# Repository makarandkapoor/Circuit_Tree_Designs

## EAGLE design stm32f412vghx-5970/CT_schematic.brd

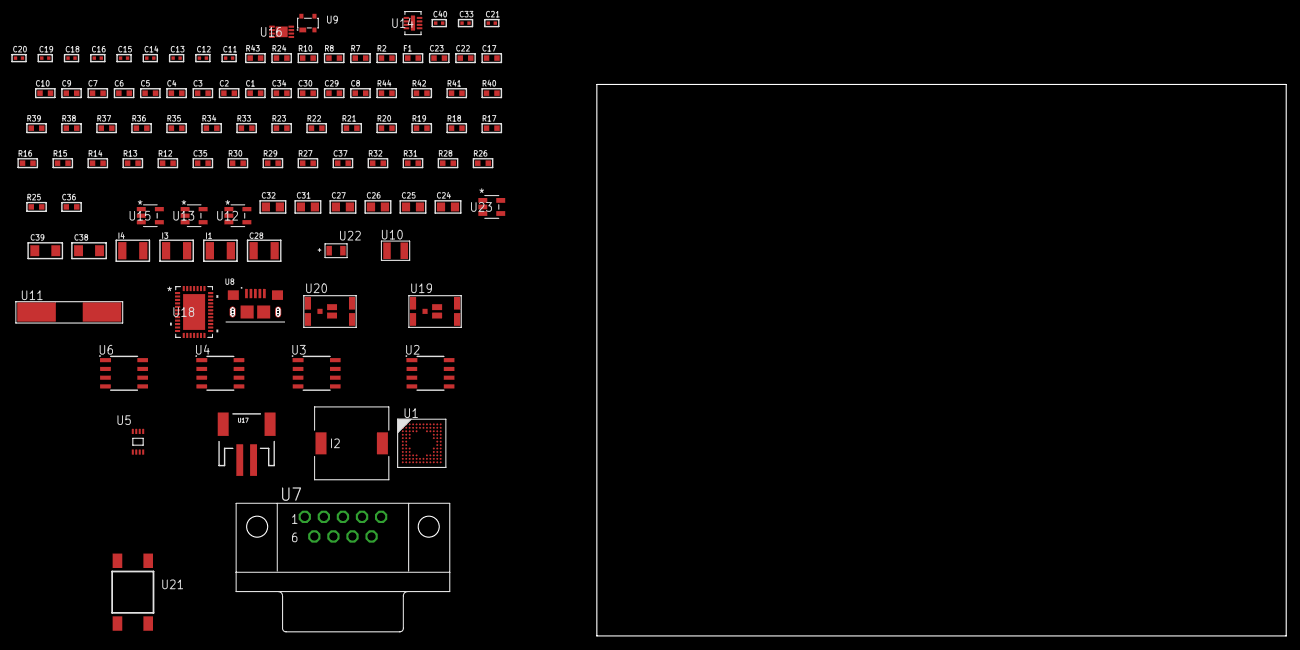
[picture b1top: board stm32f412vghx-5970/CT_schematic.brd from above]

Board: 2 copper layers, 105 parts (0 on the bottom side), 76 nets, no tracks yet.

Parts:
C1, C10, C17, C22, C23: 1e-06; C0603
C2, C3, C4, C5, C6, C7: 1e-07; C0603
C8: 4.7e-06; C0603
C9: 1e-08; C0603
C11, C12, C33: 1e-07; C0402
C13, C14, C15, C16: 1e-11; C0402
C18, C19, C20, C21, C40: 1e-08; C0402
C24, C25, C26, C27, C31, C32: 1e-05; C0805
C28: 1e-05; C1210
C29, C34: 2.2e-06; C0603
C30: 2.2e-07; C0603
C35: 2.45e-08; R0603
C36: 2.8258362168397e-09; R0603
C37: 7.105e-09; R0603
C38, C39: 1e-05; C1206
F1: 240.0; L0603
I1, I4: 3.3e-05; L1210
I2: 7e-06; DR1040
I3: 1e-05; L1210
R2: 1000.0; R0603
R7: 4700.0; R0603
R8, R10: 2200.0; R0603
R12, R13, R14, R15, R16, R17, R18, R19, R20, R21, R22, R23, R33, R35, R36, R39, R40, R41, R44: 10000.0; R0603
R24: 120.0; R0603
R25, R26, R28, R31, R32: 1000000.0; R0603
R27: 490000.0; R0603
R29: 100000.0; R0603
R30: 560000.0; R0603
R34: 75000.0; R0603
R37, R38: 95300.0; R0603
R42: 24000.0; R0603
R43: 2000.0; R0603
U1: STM32F412VGH6; UFBGA100
U2: AT25080B-SSHL-T; SOIC-8
U3: AT25320B-SSHL-T; SOIC-8
U4: AT25512N-SH-T; SOIC-8
U5: 24AA08T-I/MNY; TDFN-8/6MM
U6: MCP2562-E/SN; SOIC-8
U7: 182-009-113R531; 182-009-MALE
U8: 10118193-0001LF; FCI_10118193-0001LF
U9: prtr5v0u2ax; SOT143B
U10: ABS07-32.768KHZ-7-T
U11: ABLS-25.000MHZ-B2F-T
U12, U13, U15: ltc3406es5; TSOT-23-5
U14: LT3494AEDDB#TRMPBF; DFN-8_DDB
U16: MCP73831T-2ACI/MC; DFN8_2X3MC
U17: S2B-PH-SM4-TB(LF)(SN); JST-2-SMD
U18: LTC2928CUHF#PBF; QFN-38_UHF
U19, U20: IRF8306MTRPbF; IRF8306MTRPBF
U21: 4-1437565-2; SW_4-1437565-2
U22: Q65110A2395; LGM67K-G1J2-24-Z
U23: nc7sz125m5x; NC7SZ125M5X

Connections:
CLK_CRYSTAL_U1_D1: C13.1, U1.D1, U10.1
CLK_CRYSTAL_U1_E1: C14.1, U1.E1, U10.2
CLK_CRYSTAL_U1_F1: C15.1, U1.F1, U11.1
CLK_CRYSTAL_U1_G1: C16.1, U1.G1, U11.2
GND: C1.2, C2.2, C3.2, C4.2, C5.2, C6.2, C7.2, C8.2, C9.2, C10.2, C11.2, C12.2, C13.2, C14.2, C15.2, C16.2, C17.2, C18.2, C19.2, C20.2, C21.2, C22.2, C23.2, C24.2, C25.1, C25.2, C26.2, C27.1, C27.2, C28.2, C29.2, C30.2, C31.2, C32.1, C32.2, C33.2, C34.2, C35.2, C36.2, C37.2, C38.2, C39.2, C40.2, R2.2, R12.2, R13.2, R25.2, R27.2, R31.2, R34.2, R37.2, R38.2, R39.2, R40.2, R41.2, R43.2, U1.B12, U1.D3, U1.F2, U1.F11, U1.F12, U1.J1, U1.K1, U2.4, U3.4, U4.4, U5.4, U6.2, U6.8, U7.5, U8.5, U8.6, U8.7, U8.8, U8.9, U9.1, U12.2, U13.2, U14.2, U14.9, U15.2, U16.6, U16.9, U17.2, U18.8, U18.9, U18.10, U18.12, U18.13, U18.24, U18.25, U18.30, U18.32, U18.39, U22.C, U23.1, U23.3
INPUT_USBPOWER_5V: C17.1, C38.1, R44.2, U1.D10, U8.1, U9.4, U16.1, U16.2
NET_U1_A3: R8.1, U1.A3, U5.6
NET_U1_A4: R12.1, U1.A4
NET_U1_B3: R10.1, U1.B3, U5.5
NET_U1_C11: C12.1, U1.C11
NET_U1_E3: R14.1, U1.E3
NET_U1_H2: R7.1, U1.H2, U23.4
NET_U1_H3: R13.1, U1.H3
NET_U1_M1: C9.1, C10.1, F1.1, U1.L1, U1.M1
NET_U1_M12: U21.3, U21.4
NET_U2_3: R15.1, U2.3
NET_U2_7: R17.1, U2.7
NET_U3_3: R18.1, U3.3
NET_U3_7: R20.1, U3.7
NET_U4_3: R21.1, U4.3
NET_U4_7: R23.1, U4.7
NET_U6_6: R24.2, U6.6
NET_U7_2: R24.2, U6.6, U7.2
NET_U7_3: R24.1, U6.7, U7.3
NET_U12_3: I1.1, U12.3
NET_U12_5: R25.1, R26.1, U12.5
NET_U12_ATNET_3: I1.2, R26.2
NET_U13_3: I2.1, U13.3
NET_U13_5: R27.1, R28.1, U13.5
NET_U13_ATNET_3: I2.2, R28.2
NET_U14_1: I3.1, U14.1
NET_U14_5: R29.1, U14.5
NET_U14_6: R30.1, U14.6
NET_U14_8: C30.1, U14.8
NET_U15_3: I4.1, U15.3
NET_U15_5: R31.1, R32.1, U15.5
NET_U15_ATNET_3: I4.2, R32.2
NET_U16_5: R44.1, U16.5
NET_U16_8: R43.1, U16.8
NET_U18_3: R40.1, U18.3
NET_U18_6: R37.1, U18.6
NET_U18_7: R38.1, U18.7
NET_U18_16: R39.1, R42.1, U18.16
NET_U18_18: R36.1, U18.18
NET_U18_19: R35.1, U18.19, U18.20
NET_U18_21: R33.1, R34.1, U18.21, U23.2
NET_U18_26: C36.1, U18.26
NET_U18_27: C35.1, U18.27
NET_U18_28: C37.1, U18.28
NET_U18_38: R41.1, U18.38
NET_U19_3: U18.2, U19.3
NET_U20_3: U18.37, U20.3
NET_U21_1: R2.1, U21.1, U21.2
PROC_CAN1_RX: U1.C9, U6.4
PROC_CAN1_TX: U1.B9, U6.1
PROC_SPI1_MISO: U1.A7, U2.2
PROC_SPI1_MOSI: U1.C5, U2.5
PROC_SPI1_NSS: R16.1, U1.A9, U2.1
PROC_SPI1_SCK: U1.A8, U2.6
PROC_SPI2_MISO: U1.J3, U4.2
PROC_SPI2_MOSI: U1.K2, U4.5
PROC_SPI2_NSS: R22.1, U1.L12, U4.1
PROC_SPI2_SCK: U1.B8, U4.6
PROC_SPI3_MISO: U1.C10, U3.2
PROC_SPI3_MOSI: U1.B6, U3.5
PROC_SPI3_NSS: R19.1, U1.M3, U3.1
PROC_SPI3_SCK: U1.B11, U3.6
PROC_USB_OTG_FS_DM: U1.B12, U8.2, U9.3
PROC_USB_OTG_FS_DP: U1.A12, U8.3, U9.2
VCC_3V7: C33.1, C34.1, C39.1, R33.2, R35.2, R36.2, R42.2, U16.3, U16.4, U17.1, U18.11, U18.22, U19.1, U19.2, U19.6, U19.7, U20.1, U20.2, U20.6, U20.7
VCC_S1_3V7: C24.1, C26.1, C28.1, I3.2, R29.2, U12.4, U13.4, U14.3, U14.4, U19.4, U19.5
VCC_S2_3V7: C31.1, U15.4, U20.4, U20.5
VCC_TIER1_1V2: C11.1, C25.2, I1.2, R26.2, U1.L11
VCC_TIER1_1V8: C1.1, C2.1, C3.1, C4.1, C5.1, C6.1, C7.1, C8.1, C18.1, C19.1, C20.1, C21.1, C23.1, C27.2, C40.1, F1.2, I2.2, R7.2, R8.2, R10.2, R14.2, R15.2, R16.2, R17.2, R18.2, R19.2, R20.2, R21.2, R22.2, R23.2, R28.2, U1.C4, U1.E2, U1.G2, U1.G11, U1.G12, U2.8, U3.8, U4.8, U5.7, U5.8, U6.5, U23.5
VCC_TIER1_5V0: C22.1, C29.1, R30.2, U6.3, U14.7
VCC_TIER2_1V2: C32.2, I4.2, R32.2

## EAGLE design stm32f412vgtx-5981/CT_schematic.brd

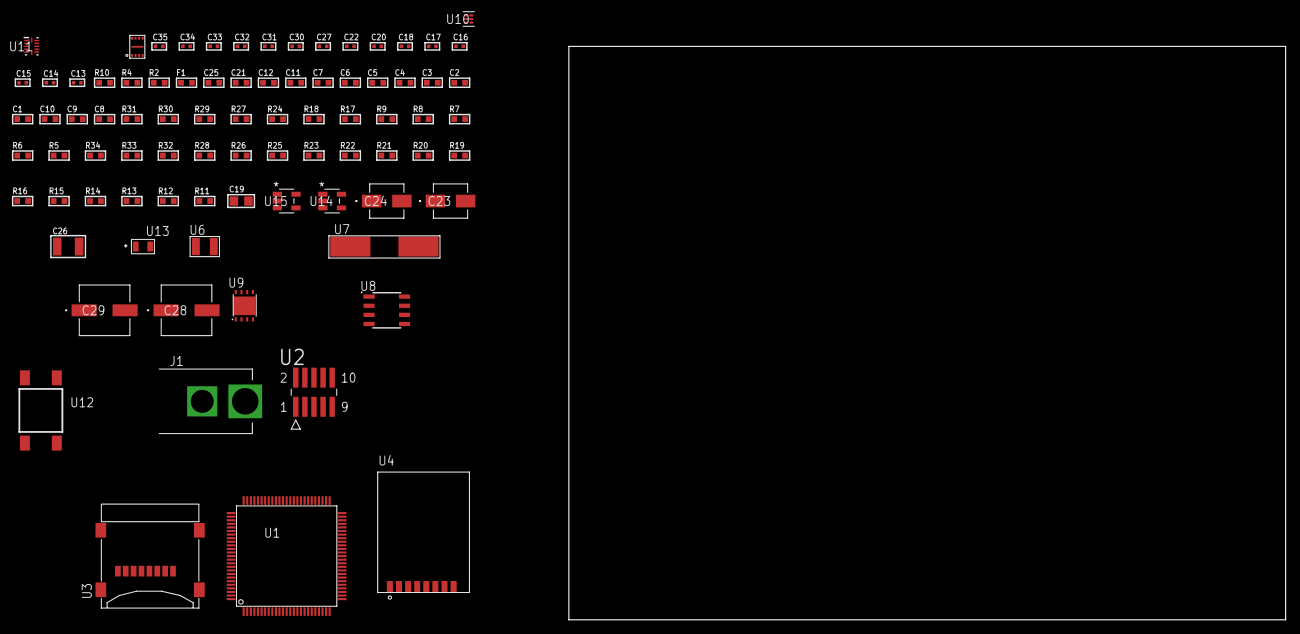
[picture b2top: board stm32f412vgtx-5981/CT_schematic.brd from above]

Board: 2 copper layers, 100.0 x 80.0 mm, 84 parts (0 on the bottom side), 47 nets, no tracks yet.

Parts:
C1, C12, C21: 1e-06; C0603
C2, C3, C4, C5, C6, C7: 1e-07; C0603
C8: 4.7e-06; C0603
C9, C10: 2.2e-06; C0603
C11: 1e-08; C0603
C13, C14, C15, C16: 1e-11; C0402
C17, C18, C20, C22, C27, C31, C33: 1e-07; C0402
C19: 1e-05; C0805
C23: 1e-06; EXV-9B
C24: 2.2e-06; EXV-9B
C25: 8e-07; R0603
C26: 1e-05; C1210
C28, C29: 0.0001; EXV-9H
C30, C32, C34, C35: 1e-08; C0402
F1: 240.0; L0603
J1: PJ-037B; PJ-037B_PACKAGE
R2: 1000.0; R0603
R4: 4700.0; R0603
R5, R6, R7, R8, R9, R17, R18, R29, R30: 10000.0; R0603
R10: 5.0; R0603
R11, R12, R13, R14, R15, R16, R19, R20, R21, R22, R23, R25, R26, R28: 100000.0; R0603
R24: 47000.0; R0603
R27: 91000.0; R0603
R31: 82000.0; R0603
R32: 300000.0; R0603
R33: 120000.0; R0603
R34: 200000.0; R0603
U1: STM32F412VGT6; LQFP100
U2: FTSH-105-01-L-DV-K; SAMTEC_FTSH-105-01-L-DV-K
U3: 0472192001; MOLEX_47219-2001
U4: RFM75-S
U5: SST26WF040BT-104I/NP; USON-8
U6: ABS07-32.768KHZ-7-T
U7: ABLS-25.000MHZ-B2F-T
U8: LP2954AIMX/NOPB; LP2954
U9: LP2951ACSDX/NOPB; WSON-8
U10: TPS3895ADRYR; SON-6
U11: LSF0204DRUTR; RUT0012A
U12: 4-1437565-2; SW_4-1437565-2
U13: Q65110A2395; LGM67K-G1J2-24-Z
U14, U15: nc7sz125m5x; NC7SZ125M5X

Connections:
CLK_CRYSTAL_U1_8: C13.1, U1.8, U6.1
CLK_CRYSTAL_U1_9: C14.1, U1.9, U6.2
CLK_CRYSTAL_U1_12: C15.1, U1.12, U7.1
CLK_CRYSTAL_U1_13: C16.1, U1.13, U7.2
GND: C1.2, C2.2, C3.2, C4.2, C5.2, C6.2, C7.2, C8.2, C9.2, C10.2, C11.2, C12.2, C13.2, C14.2, C15.2, C16.2, C17.2, C18.2, C19.2, C20.2, C21.2, C22.2, C23.2, C24.2, C25.2, C26.2, C27.2, C28.2, C29.2, C30.2, C31.2, C32.2, C33.2, C34.2, C35.2, J1.2, R2.2, R5.2, R9.2, R10.2, R25.2, R28.2, R31.2, R33.2, U1.10, U1.20, U1.27, U1.49, U1.74, U1.99, U2.3, U2.5, U3.6, U3.G1, U3.G2, U3.G3, U3.G4, U4.1, U5.4, U5.9, U8.4, U9.3, U9.4, U9.PAD, U10.2, U11.6, U13.C, U14.2, U14.3, U15.1, U15.3
NET_U1_14: R4.1, U1.14, U15.4
NET_U1_22: C11.1, C12.1, F1.1, U1.21, U1.22
NET_U1_48: C9.1, U1.48
NET_U1_73: C10.1, U1.73
NET_U1_94: R5.1, U1.94
NET_U1_98: U12.3, U12.4
NET_U2_9: R10.1, U2.9
NET_U4_3: R17.1, U4.3
NET_U8_3: R23.1, U8.3
NET_U8_5: R22.1, U8.5
NET_U8_7: R24.2, R25.1, U8.7
NET_U9_5: R26.1, U9.5
NET_U9_7: R27.2, R28.1, U9.7
NET_U10_1: R30.1, R31.1, U10.1
NET_U10_3: R32.2, R33.1, U10.3
NET_U10_4: R29.1, U10.4, U14.4, U15.2
NET_U11_12: R34.1, U11.12
NET_U12_1: R2.1, U12.1, U12.2
PROC_QUADSPI_BK1_IO0: U1.58, U5.5
PROC_QUADSPI_BK1_IO1: U1.59, U5.2
PROC_QUADSPI_BK1_IO2: R20.1, U1.1, U5.3
PROC_QUADSPI_BK1_IO3: R21.1, U1.24, U5.7
PROC_QUADSPI_BK1_NCS: R19.1, U1.92, U5.1
PROC_QUADSPI_CLK: U1.36, U5.6
PROC_SDIO_CK: R12.1, U1.54, U3.5
PROC_SDIO_CMD: R11.1, U1.83, U3.3
PROC_SDIO_D0: R13.1, U1.65, U3.7
PROC_SDIO_D1: R14.1, U1.66, U3.8
PROC_SDIO_D2: R15.1, U1.68, U3.1
PROC_SDIO_D3: R16.1, U1.79, U3.2
PROC_SPI1_MISO_TOXCVR: U4.7, U11.9
PROC_SPI1_MOSI_TOXCVR: U4.6, U11.10
PROC_SPI1_NSS_TOXCVR: R18.1, U4.4, U11.7
PROC_SPI1_SCK_TOXCVR: U4.5, U11.8
PROC_SYS_JTCK_SWCLK: R9.1, U1.76, U2.4
PROC_SYS_JTDI: R7.1, U1.77, U2.8
PROC_SYS_JTDO_SWO: U1.89, U2.6
PROC_SYS_JTMS_SWDIO: R8.1, U1.72, U2.2
RST_OUT_U2_JTAG_RST_B: R6.1, U2.10, U14.1
VCC_S1_12V3: C23.1, C25.1, C28.1, C29.1, J1.1, R23.2, U8.8, U9.8
VCC_TIER1_1V8: C1.1, C2.1, C3.1, C4.1, C5.1, C6.1, C7.1, C8.1, C17.1, C18.1, C19.1, C22.1, C24.1, C27.1, C32.1, C33.1, C34.1, C35.1, F1.2, R4.2, R6.2, R7.2, R8.2, R11.2, R12.2, R13.2, R14.2, R15.2, R16.2, R19.2, R20.2, R21.2, R22.2, R24.1, R29.2, R30.2, R32.1, R34.2, U1.6, U1.11, U1.19, U1.28, U1.50, U1.75, U1.100, U2.1, U3.4, U5.8, U8.1, U10.6, U11.1, U14.5, U15.5
VCC_TIER1_2V5: C20.1, C21.1, C26.1, C30.1, C31.1, R17.2, R18.2, R26.2, R27.1, U4.2, U9.1, U11.11

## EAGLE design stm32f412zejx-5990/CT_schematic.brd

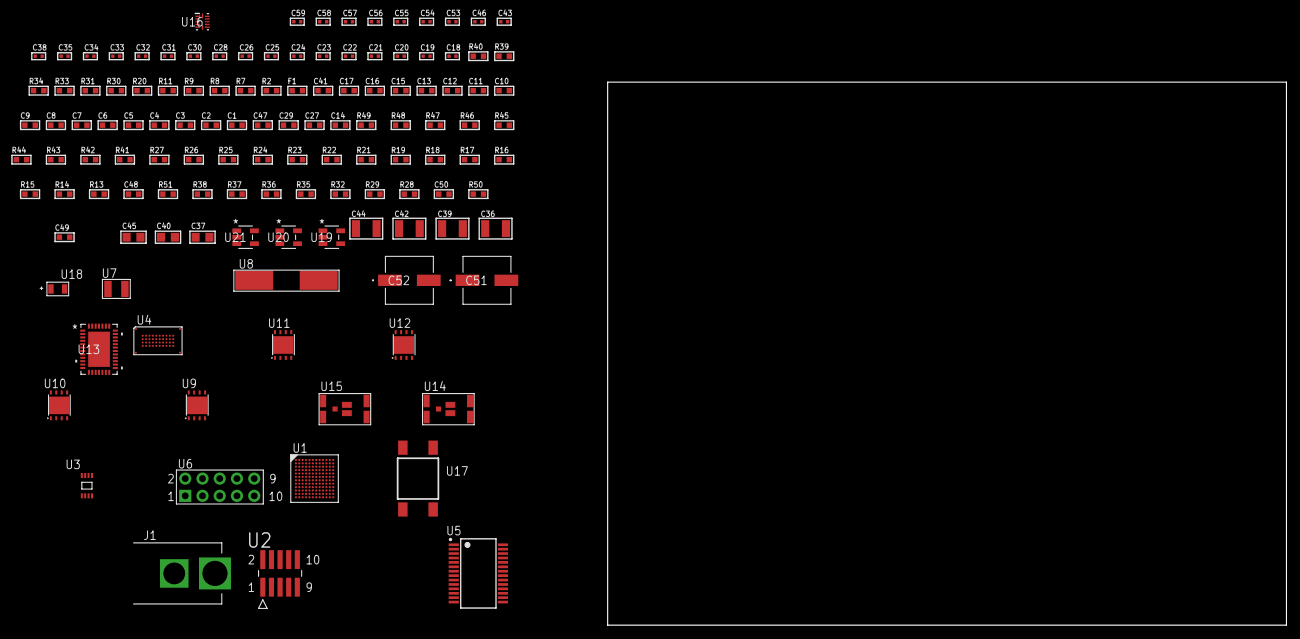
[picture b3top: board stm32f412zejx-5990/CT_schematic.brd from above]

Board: 2 copper layers, 100.0 x 80.0 mm, 126 parts (0 on the bottom side), 103 nets, no tracks yet.

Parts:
C1, C16: 1e-06; C0603
C2, C3, C4, C5, C6, C7, C8, C9, C10, C11, C12, C13, C17: 1e-07; C0603
C14: 4.7e-06; C0603
C15: 1e-08; C0603
C18, C19, C24, C26, C28, C30, C31, C32, C33, C34, C46, C54, C56: 1e-07; C0402
C20, C21, C22, C23: 1e-11; C0402
C25, C35, C38, C43, C53, C55, C57, C58, C59: 1e-08; C0402
C27, C29, C47: 2.2e-06; C0603
C36, C39, C42, C44: 1e-05; C1210
C37, C40, C45: 1e-05; C0805
C41: 8e-07; R0603
C48: 2.45e-08; R0603
C49: 2.8258362168397e-09; R0603
C50: 7.105e-09; R0603
C51, C52: 0.0001; EXV-9H
F1: 240.0; L0603
J1: PJ-037B; PJ-037B_PACKAGE
R2, R31, R34, R40: 1000.0; R0603
R7, R8: 4700.0; R0603
R9, R11: 2200.0; R0603
R13, R14, R15, R16, R17, R18, R19, R21, R22, R23, R24, R25, R26, R27, R41, R43, R44, R47, R48, R49: 10000.0; R0603
R20: 5.0; R0603
R28, R29, R32, R35, R37, R38: 100000.0; R0603
R30, R39: 200.0; R0603
R33: 806.0; R0603
R36: 130000.0; R0603
R42: 75000.0; R0603
R45, R46: 95300.0; R0603
R50: 100672.72727273; R0603
R51: 200000.0; R0603
U1: STM32F412ZEJ6; UFBGA144
U2: FTSH-105-01-L-DV-K; SAMTEC_FTSH-105-01-L-DV-K
U3: 24AA64T-I/MNY; TDFN-8/6MM
U4: S29VS256RABBHW000
U5: ST3241EBPR; SSOP-28
U6: HTSS-105-01-G-D
U7: ABS07-32.768KHZ-7-T
U8: ABLS-25.000MHZ-B2F-T
U9, U10, U12: LP3878SDX-ADJ/NOPB; WSON-8
U11: LP2951ACSDX/NOPB; WSON-8
U13: LTC2928CUHF#PBF; QFN-38_UHF
U14, U15: IRF8306MTRPbF; IRF8306MTRPBF
U16: LSF0204DRUTR; RUT0012A
U17: 4-1437565-2; SW_4-1437565-2
U18: Q65110A2395; LGM67K-G1J2-24-Z
U19, U20, U21: nc7sz125m5x; NC7SZ125M5X

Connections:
CLK_CRYSTAL_U1_B1: C20.1, U1.B1, U7.1
CLK_CRYSTAL_U1_C1: C21.1, U1.C1, U7.2
CLK_CRYSTAL_U1_D1: C22.1, U1.D1, U8.1
CLK_CRYSTAL_U1_E1: C23.1, U1.E1, U8.2
GND: C1.2, C2.2, C3.2, C4.2, C5.2, C6.2, C7.2, C8.2, C9.2, C10.2, C11.2, C12.2, C13.2, C14.2, C15.2, C16.2, C17.2, C18.2, C19.2, C20.2, C21.2, C22.2, C23.2, C24.2, C25.2, C26.2, C27.2, C28.2, C29.2, C30.2, C33.2, C34.2, C35.2, C36.2, C37.2, C38.2, C39.2, C40.2, C41.2, C42.2, C43.2, C44.2, C45.2, C46.2, C47.2, C48.2, C49.2, C50.2, C51.2, C52.2, C53.2, C54.2, C55.2, C56.2, C57.2, C58.2, C59.2, J1.2, R2.2, R13.2, R14.2, R19.2, R20.2, R23.2, R31.2, R34.2, R37.2, R40.2, R42.2, R45.2, R46.2, R47.2, R48.2, R49.2, U1.D2, U1.E6, U1.E7, U1.G4, U1.G8, U1.G10, U1.H6, U1.J1, U1.K1, U2.3, U2.5, U3.4, U4.C5, U4.D12, U4.E3, U4.F5, U5.23, U5.25, U6.9, U9.3, U9.PAD, U10.3, U10.PAD, U11.3, U11.4, U11.PAD, U12.3, U12.PAD, U13.8, U13.9, U13.10, U13.12, U13.13, U13.24, U13.25, U13.30, U13.32, U13.39, U16.6, U18.C, U19.2, U19.3, U20.1, U20.3, U21.1, U21.3
NET_U1_B5: R11.1, U1.B5, U3.5
NET_U1_C5: R9.1, U1.C5, U3.6
NET_U1_D5: R13.1, U1.D5
NET_U1_E5: R14.1, U1.E5
NET_U1_F1: R8.1, U1.F1, U21.4
NET_U1_G9: C19.1, U1.G9
NET_U1_H5: R15.1, U1.H5
NET_U1_M1: C15.1, C16.1, F1.1, U1.L1, U1.M1
NET_U1_M12: U17.3, U17.4
NET_U2_9: R20.1, U2.9
NET_U3_1: R21.1, U3.1
NET_U3_2: R22.1, U3.2
NET_U3_3: R23.1, U3.3
NET_U4_D8: R7.1, U4.D8, U20.4
NET_U5_1: C32.1, U5.1
NET_U5_2: C32.2, U5.2
NET_U5_3: C34.1, U5.3
NET_U5_22: R28.1, U5.22
NET_U5_24: C31.2, U5.24
NET_U5_27: C33.1, U5.27
NET_U5_28: C31.1, U5.28
NET_U6_3: U5.4, U6.3
NET_U6_4: U5.5, U6.4
NET_U6_5: U5.9, U6.5
NET_U6_6: U5.10, U6.6
NET_U9_1: C35.1, U9.1
NET_U9_6: R30.2, R31.1, U9.6
NET_U9_8: R29.1, U9.8
NET_U10_1: C38.1, U10.1
NET_U10_6: R33.2, R34.1, U10.6
NET_U10_8: R32.1, U10.8
NET_U11_5: R35.1, U11.5
NET_U11_7: R36.2, R37.1, U11.7
NET_U12_1: C43.1, U12.1
NET_U12_6: R39.2, R40.1, U12.6
NET_U12_8: R38.1, U12.8
NET_U13_3: R48.1, U13.3
NET_U13_6: R45.1, U13.6
NET_U13_7: R46.1, U13.7
NET_U13_16: R47.1, R50.1, U13.16
NET_U13_18: R44.1, U13.18
NET_U13_19: R43.1, U13.19, U13.20
NET_U13_21: R41.1, R42.1, U13.21, U19.4, U20.2, U21.2
NET_U13_22: C46.1, R41.2, R43.2, R44.2, U13.11, U13.22
NET_U13_26: C49.1, U13.26
NET_U13_27: C48.1, U13.27
NET_U13_28: C50.1, U13.28
NET_U13_38: R49.1, U13.38
NET_U14_3: U13.2, U14.3
NET_U15_3: U13.37, U15.3
NET_U16_12: R51.1, U16.12
NET_U17_1: R2.1, U17.1, U17.2
PROC_FSMC_A16: U1.H9, U4.D4
PROC_FSMC_A17: U1.L10, U4.C11
PROC_FSMC_A18: U1.K10, U4.D10
PROC_FSMC_A19: U1.A2, U4.C10
PROC_FSMC_A20: U1.B2, U4.D5
PROC_FSMC_A21: U1.B3, U4.C4
PROC_FSMC_A22: U1.B4, U4.C12
PROC_FSMC_A23: U1.A3, U4.D7
PROC_FSMC_CLK: U1.D9, U4.C6
PROC_FSMC_D0: U1.K11, U4.F3
PROC_FSMC_D1: U1.G12, U4.F4
PROC_FSMC_D2: U1.B10, U4.E6
PROC_FSMC_D3: U1.C10, U4.E7
PROC_FSMC_D4: U1.L2, U4.F8
PROC_FSMC_D5: U1.L7, U4.F9
PROC_FSMC_D6: U1.J3, U4.E10
PROC_FSMC_D7: U1.J7, U4.E11
PROC_FSMC_D8: U1.H8, U4.E4
PROC_FSMC_D9: U1.J8, U4.E5
PROC_FSMC_D10: U1.K8, U4.F6
PROC_FSMC_D11: U1.L8, U4.F7
PROC_FSMC_D12: U1.M8, U4.E8
PROC_FSMC_D13: U1.L9, U4.E9
PROC_FSMC_D14: U1.K9, U4.F11
PROC_FSMC_D15: U1.J9, U4.F12
PROC_FSMC_NE4: R25.1, U1.B8, U4.D11
PROC_FSMC_NL: U1.D6, U4.D6
PROC_FSMC_NOE: R27.1, U1.C9, U4.E12
PROC_FSMC_NWAIT: R24.1, U1.A8, U4.C3
PROC_FSMC_NWE: R26.1, U1.B9, U4.C8
PROC_SYS_JTCK_SWCLK: R19.1, U1.A11, U2.4
PROC_SYS_JTDI: R17.1, U1.A10, U2.8
PROC_SYS_JTDO_SWO: U1.A7, U2.6
PROC_SYS_JTMS_SWDIO: R18.1, U1.A12, U2.2
PROC_USART1_CTS_TOXCVR: U5.13, U16.7
PROC_USART1_RTS_TOXCVR: U5.18, U16.9
PROC_USART1_RX_TOXCVR: U5.19, U16.10
PROC_USART1_TX_TOXCVR: U5.14, U16.8
RST_OUT_U2_JTAG_RST_B: R16.1, U2.10, U19.1
VCC_12V4: C47.1, C51.1, C52.1, J1.1, R50.2, U13.23, U14.1, U14.2, U14.6, U14.7, U15.1, U15.2, U15.6, U15.7
VCC_S1_12V4: C36.1, C39.1, C41.1, R29.2, R32.2, U9.4, U10.4, U11.8, U14.4, U14.5
VCC_S2_12V4: C44.1, R38.2, U12.4, U15.4, U15.5
VCC_TIER1_1V2: C18.1, C37.1, R30.1, U1.H7, U9.5
VCC_TIER1_1V8: C1.1, C2.1, C3.1, C4.1, C5.1, C6.1, C7.1, C8.1, C9.1, C10.1, C11.1, C12.1, C13.1, C14.1, C17.1, C24.1, C25.1, C26.1, C27.1, C28.1, C29.1, C40.1, C55.1, C56.1, C57.1, C58.1, C59.1, F1.2, R7.2, R8.2, R9.2, R11.2, R15.2, R16.2, R17.2, R18.2, R21.2, R22.2, R24.2, R25.2, R26.2, R27.2, R33.1, R51.2, U1.C2, U1.C11, U1.D3, U1.F4, U1.F5, U1.F6, U1.F7, U1.F8, U1.F9, U1.F10, U1.G5, U1.G6, U1.G7, U2.1, U3.7, U3.8, U4.C7, U4.D3, U4.F10, U10.5, U16.1, U19.5, U20.5, U21.5
VCC_TIER1_3V0: C30.1, C42.1, C53.1, C54.1, R28.2, R35.2, R36.1, U5.26, U11.1, U16.11
VCC_TIER2_1V2: C45.1, R39.1, U12.5

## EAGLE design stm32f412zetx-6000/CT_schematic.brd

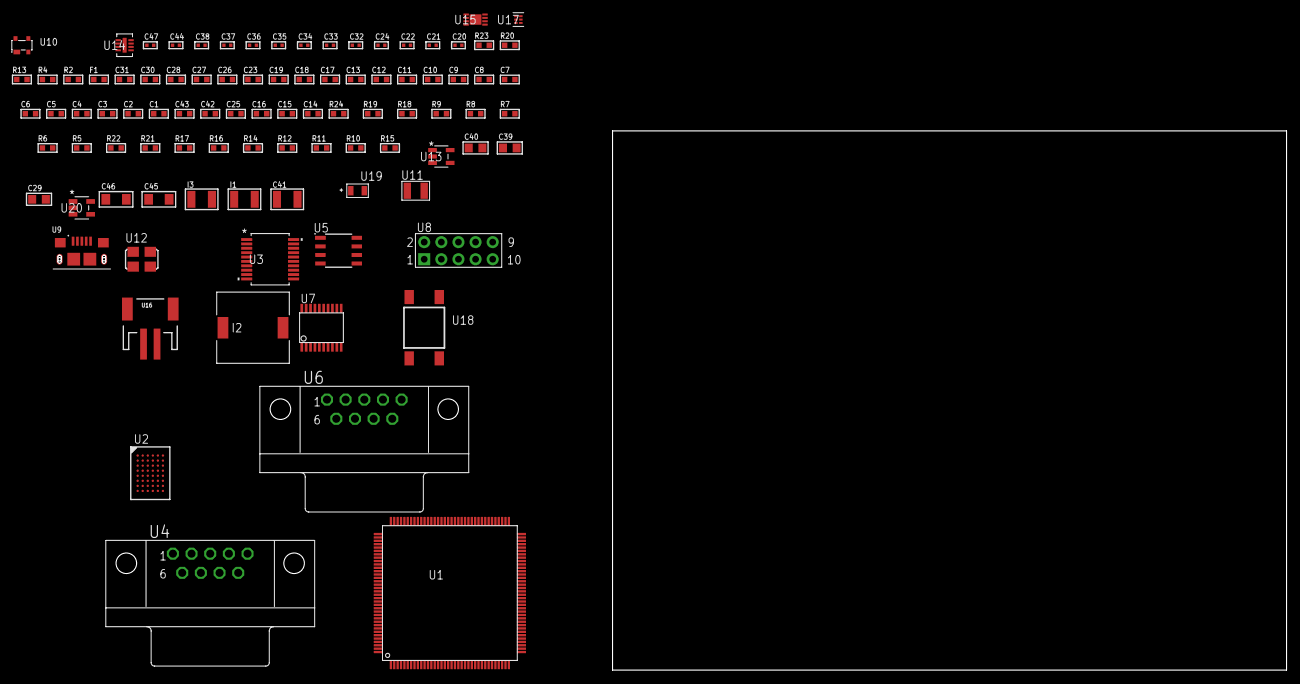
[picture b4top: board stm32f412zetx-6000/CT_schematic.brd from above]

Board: 2 copper layers, 93 parts (0 on the bottom side), 103 nets, no tracks yet.

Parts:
C1, C18, C23, C26, C27, C28, C30, C31: 1e-06; C0603
C2, C3, C4, C5, C6, C7, C8, C9, C10, C11, C12, C13, C19: 1e-07; C0603
C14: 4.7e-06; C0603
C15, C16, C25, C42: 2.2e-06; C0603
C17: 1e-08; C0603
C20, C24, C32, C33, C34, C35, C36, C37, C44: 1e-07; C0402
C21, C22: 1e-11; C0402
C29: 4.7e-06; C0805
C38, C47: 1e-08; C0402
C39, C40: 1e-05; C0805
C41: 1e-05; C1210
C43: 2.2e-07; C0603
C45, C46: 1e-05; C1206
F1: 240.0; L0603
I1: 1.5e-05; L1210
I2: 3.8e-06; DR1040
I3: 1e-05; L1210
R2: 1000.0; R0603
R4: 4700.0; R0603
R5, R6, R7, R8, R9, R18, R19, R24: 10000.0; R0603
R10, R11, R12, R16: 100000.0; R0603
R13: 120.0; R0603
R14: 220000.0; R0603
R15: 1000000.0; R0603
R17: 560000.0; R0603
R20: 9100.0; R0603
R21: 680000.0; R0603
R22: 120000.0; R0603
R23: 2000.0; R0603
U1: STM32F412ZET6; LQFP144
U2: CY62147GE30-45BVXI; VFBGA48
U3: MAX3218EAP+T; SSOP-20
U4, U6: 182-009-113R531; 182-009-MALE
U5: MCP2562-E/SN; SOIC-8
U7: SP3203ECY-L/TR; TSSOP20-I
U8: HTSS-105-01-G-D
U9: 10118193-0001LF; FCI_10118193-0001LF
U10: prtr5v0u2ax; SOT143B
U11: ABS07-32.768KHZ-7-T
U12: ASFL1-25MHZ-NCS; ASFL1
U13: ltc3406es5; TSOT-23-5
U14: LT3494AEDDB#TRMPBF; DFN-8_DDB
U15: MCP73831T-2ACI/MC; DFN8_2X3MC
U16: S2B-PH-SM4-TB(LF)(SN); JST-2-SMD
U17: TPS3895ADRYR; SON-6
U18: 4-1437565-2; SW_4-1437565-2
U19: Q65110A2395; LGM67K-G1J2-24-Z
U20: nc7sz125m5x; NC7SZ125M5X

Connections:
CLK_CRYSTAL_U1_8: C21.1, U1.8, U11.1
CLK_CRYSTAL_U1_9: C22.1, U1.9, U11.2
CLK_U1_23: U1.23, U12.3
GND: C1.2, C2.2, C3.2, C4.2, C5.2, C6.2, C7.2, C8.2, C9.2, C10.2, C11.2, C12.2, C13.2, C14.2, C15.2, C16.2, C17.2, C18.2, C19.2, C20.2, C21.2, C22.2, C23.2, C24.2, C25.2, C26.2, C27.2, C28.2, C30.2, C31.2, C32.2, C33.2, C36.2, C37.2, C38.2, C39.2, C40.1, C40.2, C41.2, C42.2, C43.2, C44.2, C45.2, C46.2, C47.2, R2.2, R5.2, R6.2, R14.2, R20.2, R22.2, R23.2, U1.16, U1.31, U1.38, U1.51, U1.61, U1.83, U1.94, U1.103, U1.107, U1.120, U1.130, U2.D1, U2.E6, U3.5, U3.17, U3.20, U4.5, U5.2, U5.8, U6.5, U7.18, U8.9, U9.5, U9.6, U9.7, U9.8, U9.9, U10.1, U12.2, U13.2, U14.2, U14.9, U15.6, U15.9, U16.2, U17.2, U19.C, U20.1, U20.3
INPUT_USBPOWER_5V: C23.1, C45.1, R24.2, U1.101, U9.1, U10.4, U15.1, U15.2
NET_U1_25: R4.1, U1.25, U20.4
NET_U1_33: C17.1, C18.1, F1.1, U1.32, U1.33
NET_U1_71: C15.1, U1.71
NET_U1_106: C16.1, U1.106
NET_U1_138: R5.1, U1.138
NET_U1_142: U18.3, U18.4
NET_U1_143: R6.1, U1.143
NET_U3_1: I1.1, U3.1
NET_U3_2: R10.1, U3.2
NET_U3_3: R11.1, U3.3
NET_U3_4: R12.1, U3.4
NET_U3_15: C28.1, U3.15
NET_U3_16: C29.2, U3.16
NET_U3_18: C29.1, U3.18
NET_U3_19: C27.1, U3.19
NET_U4_2: U3.12, U4.2
NET_U4_3: U3.14, U4.3
NET_U4_7: U3.11, U4.7
NET_U4_8: U3.13, U4.8
NET_U5_6: R13.2, U5.6
NET_U6_2: R13.2, U5.6, U6.2
NET_U6_3: R13.1, U5.7, U6.3
NET_U7_1: C34.1, U7.1
NET_U7_2: C36.1, U7.2
NET_U7_3: C34.2, U7.3
NET_U7_4: C35.1, U7.4
NET_U7_5: C35.2, U7.5
NET_U7_6: C37.1, U7.6
NET_U8_3: U7.14, U8.3
NET_U8_4: U7.13, U8.4
NET_U8_5: U7.17, U8.5
NET_U8_6: U7.16, U8.6
NET_U13_3: I2.1, U13.3
NET_U13_5: R14.1, R15.1, U13.5
NET_U13_ATNET_3: I2.2, R15.2
NET_U14_1: I3.1, U14.1
NET_U14_5: R16.1, U14.5
NET_U14_6: R17.1, U14.6
NET_U14_8: C43.1, U14.8
NET_U15_5: R24.1, U15.5
NET_U15_8: R23.1, U15.8
NET_U17_1: R19.1, R20.1, U17.1
NET_U17_3: R21.2, R22.1, U17.3
NET_U17_4: R18.1, U17.4, U20.2
NET_U18_1: R2.1, U18.1, U18.2
PROC_CAN1_RX: U1.114, U5.4
PROC_CAN1_TX: U1.115, U5.1
PROC_FSMC_A0: U1.10, U2.A3
PROC_FSMC_A1: U1.11, U2.A4
PROC_FSMC_A2: U1.12, U2.A5
PROC_FSMC_A3: U1.13, U2.B3
PROC_FSMC_A4: U1.14, U2.B4
PROC_FSMC_A5: U1.15, U2.C3
PROC_FSMC_A6: U1.50, U2.C4
PROC_FSMC_A7: U1.53, U2.D4
PROC_FSMC_A8: U1.54, U2.H2
PROC_FSMC_A9: U1.55, U2.H3
PROC_FSMC_A10: U1.56, U2.H4
PROC_FSMC_A11: U1.57, U2.H5
PROC_FSMC_A12: U1.87, U2.G3
PROC_FSMC_A13: U1.88, U2.G4
PROC_FSMC_A14: U1.89, U2.F3
PROC_FSMC_A15: U1.90, U2.F4
PROC_FSMC_A16: U1.80, U2.E4
PROC_FSMC_A17: U1.81, U2.D3
PROC_FSMC_D0: U1.85, U2.B6
PROC_FSMC_D1: U1.86, U2.C5
PROC_FSMC_D2: U1.112, U2.C6
PROC_FSMC_D3: U1.113, U2.D5
PROC_FSMC_D4: U1.36, U2.E5
PROC_FSMC_D5: U1.37, U2.F5
PROC_FSMC_D6: U1.40, U2.F6
PROC_FSMC_D7: U1.41, U2.G6
PROC_FSMC_D8: U1.64, U2.B1
PROC_FSMC_D9: U1.65, U2.C1
PROC_FSMC_D10: U1.66, U2.C2
PROC_FSMC_D11: U1.67, U2.D2
PROC_FSMC_D12: U1.68, U2.E2
PROC_FSMC_D13: U1.73, U2.F2
PROC_FSMC_D14: U1.78, U2.F1
PROC_FSMC_D15: U1.79, U2.G1
PROC_FSMC_NBL0: U1.141, U2.A1
PROC_FSMC_NE4: R8.1, U1.44, U2.B5
PROC_FSMC_NOE: R7.1, U1.45, U2.A2
PROC_FSMC_NWE: R9.1, U1.28, U2.G5
PROC_USART2_CTS: U1.34, U3.8
PROC_USART2_RTS: U1.35, U3.10
PROC_USART2_RX: U1.122, U3.9
PROC_USART2_TX: U1.119, U3.7
PROC_USART3_CTS: U1.74, U7.8
PROC_USART3_RTS: U1.75, U7.10
PROC_USART3_RX: U1.70, U7.11
PROC_USART3_TX: U1.69, U7.7
PROC_USB_OTG_FS_DM: U1.103, U9.2, U10.3
PROC_USB_OTG_FS_DP: U1.104, U9.3, U10.2
VCC_S1_3V7: C39.1, C41.1, C46.1, I3.2, R16.2, U13.4, U14.3, U14.4, U15.3, U15.4, U16.1
VCC_TIER1_3V3: C1.1, C2.1, C3.1, C4.1, C5.1, C6.1, C7.1, C8.1, C9.1, C10.1, C11.1, C12.1, C13.1, C14.1, C19.1, C20.1, C24.1, C25.1, C26.1, C31.1, C32.1, C33.1, C38.1, C40.2, C44.1, C47.1, F1.2, I1.2, I2.2, R4.2, R7.2, R8.2, R9.2, R10.2, R11.2, R12.2, R15.2, R18.2, R19.2, R21.1, U1.6, U1.17, U1.30, U1.39, U1.52, U1.62, U1.72, U1.84, U1.95, U1.108, U1.121, U1.131, U1.144, U2.D6, U2.E1, U3.6, U5.5, U7.12, U7.19, U12.4, U17.6, U20.5
VCC_TIER1_5V0: C30.1, C42.1, R17.2, U5.3, U14.7

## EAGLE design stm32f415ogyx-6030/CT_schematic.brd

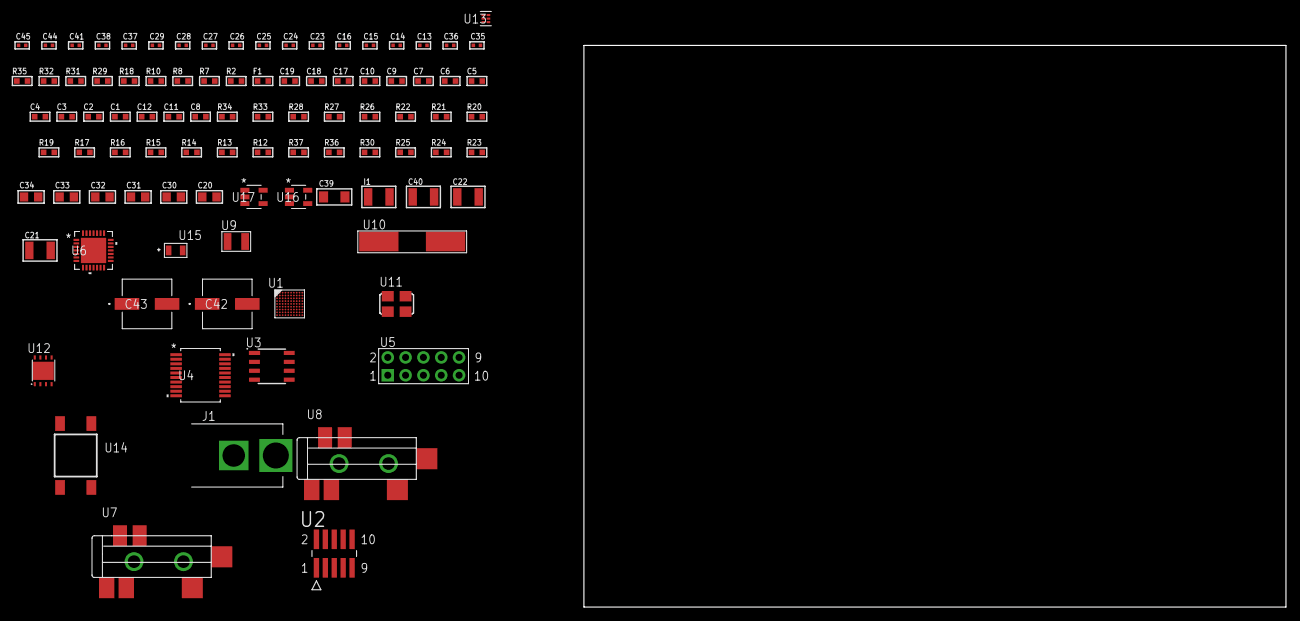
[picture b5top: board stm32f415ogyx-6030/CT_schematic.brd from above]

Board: 2 copper layers, 100.0 x 80.0 mm, 95 parts (0 on the bottom side), 56 nets, no tracks yet.

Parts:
C1, C10, C17, C18, C19: 1e-06; C0603
C2, C3, C4, C5, C6, C7: 1e-07; C0603
C8: 4.7e-06; C0603
C9: 1e-08; C0603
C11, C12: 2.2e-06; C0603
C13, C14: 1e-11; C0402
C15, C25, C26, C27, C28, C29, C41: 1e-07; C0402
C16, C37, C38, C44, C45: 1e-08; C0402
C20: 4.7e-06; C0805
C21, C22: 2.2e-05; C1210
C23, C24: 1e-09; C0402
C30, C31, C32, C33, C34: 1e-05; C0805
C35, C36: 2.2e-11; C0402
C39: 1e-05; C1206
C40: 1e-05; C1210
C42, C43: 0.0001; EXV-9H
F1: 240.0; L0603
I1: 1.5e-05; L1210
J1: PJ-037B; PJ-037B_PACKAGE
R2, R32: 1000.0; R0603
R7: 4700.0; R0603
R8, R10: 2200.0; R0603
R12, R13, R14, R15, R16, R17, R19, R20, R21, R22, R33, R34: 10000.0; R0603
R18: 5.0; R0603
R23, R24, R25, R30: 100000.0; R0603
R26, R27, R28: 47000.0; R0603
R29: 680.0; R0603
R31: 2231.0; R0603
R35: 9100.0; R0603
R36: 680000.0; R0603
R37: 120000.0; R0603
U1: STM32F415OGY6; WLCSP90
U2: FTSH-105-01-L-DV-K; SAMTEC_FTSH-105-01-L-DV-K
U3: AT24C02D-SSHM-T; AT24C02D
U4: MAX3218EAP+T; SSOP-20
U5: HTSS-105-01-G-D
U6: WM8731CLSEFL; QFN-28
U7, U8: SJ-43515TS-SMT-TR
U9: ABS07-32.768KHZ-7-T
U10: ABLS-12.288MHZ-B4-T
U11: ASFL1-25MHZ-NCS; ASFL1
U12: LP3878SDX-ADJ/NOPB; WSON-8
U13: TPS3895ADRYR; SON-6
U14: 4-1437565-2; SW_4-1437565-2
U15: Q65110A2395; LGM67K-G1J2-24-Z
U16, U17: nc7sz125m5x; NC7SZ125M5X

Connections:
CLK_CRYSTAL_U1_B9: C13.1, U1.B9, U9.1
CLK_CRYSTAL_U1_B10: C14.1, U1.B10, U9.2
CLK_CRYSTAL_U6_1: C35.1, U6.1, U10.1
CLK_CRYSTAL_U6_2: C36.1, U6.2, U10.2
CLK_U1_F10: U1.F10, U11.3
GND: C1.2, C2.2, C3.2, C4.2, C5.2, C6.2, C7.2, C8.2, C9.2, C10.2, C11.2, C12.2, C13.2, C14.2, C15.2, C16.2, C17.2, C18.2, C19.2, C24.2, C25.2, C26.2, C27.2, C28.2, C29.2, C30.2, C31.2, C32.2, C33.2, C34.2, C35.2, C36.2, C37.2, C38.2, C39.2, C40.2, C41.2, C42.2, C43.2, C44.2, C45.2, J1.2, R2.2, R13.2, R14.2, R18.2, R19.2, R21.2, R22.2, R26.2, R27.2, R28.2, R32.2, R35.2, R37.2, U1.C9, U1.E5, U1.E7, U1.E8, U1.H10, U2.3, U2.5, U3.4, U4.5, U4.17, U4.20, U5.9, U6.4, U6.15, U6.19, U6.25, U6.26, U6.29, U7.1, U8.1, U11.2, U12.3, U12.PAD, U13.2, U15.C, U16.2, U16.3, U17.1, U17.3
NET_U1_A7: R13.1, U1.A7
NET_U1_A8: R12.1, U1.A8
NET_U1_B1: C12.1, U1.B1
NET_U1_B7: R10.1, U1.B7, U3.5
NET_U1_C7: R8.1, U1.C7, U3.6
NET_U1_D9: R14.1, U1.D9
NET_U1_F4: C11.1, U1.F4
NET_U1_G9: C9.1, C10.1, F1.1, U1.G9
NET_U1_G10: R7.1, U1.G10, U17.4
NET_U1_J10: U14.3, U14.4
NET_U2_9: R18.1, U2.9
NET_U3_1: R20.1, U3.1
NET_U3_2: R21.1, U3.2
NET_U3_3: R22.1, U3.3
NET_U3_7: R19.1, U3.7
NET_U4_1: I1.1, U4.1
NET_U4_2: R23.1, U4.2
NET_U4_3: R24.1, U4.3
NET_U4_4: R25.1, U4.4
NET_U4_15: C19.1, U4.15
NET_U4_16: C20.2, U4.16
NET_U4_18: C20.1, U4.18
NET_U4_19: C18.1, U4.19
NET_U5_3: U4.12, U5.3
NET_U5_4: U4.11, U5.4
NET_U5_5: U4.14, U5.5
NET_U5_6: U4.13, U5.6
NET_U6_20: C29.1, C34.1, U6.20
NET_U7_2: C22.1, R27.1, U7.2
NET_U7_5: C21.1, R26.1, U7.5
NET_U8_5: C23.1, C24.1, R28.1, R29.1, U8.5
NET_U12_1: C38.1, U12.1
NET_U12_6: R31.2, R32.1, U12.6
NET_U12_8: R30.1, U12.8
NET_U13_1: R34.1, R35.1, U13.1
NET_U13_3: R36.2, R37.1, U13.3
NET_U13_4: R33.1, U13.4, U16.4, U17.2
NET_U14_1: R2.1, U14.1, U14.2
PROC_I2S2_CK: U1.B2, U6.7
PROC_I2S2_EXT_SD: U1.D10, U6.10
PROC_I2S2_SD: U1.E9, U6.8
PROC_I2S2_WS: U1.C3, U6.9, U6.11
PROC_SYS_JTCK_SWCLK: R16.1, U1.A2, U2.4
PROC_SYS_JTDO_SWO: U1.B6, U2.6
PROC_SYS_JTMS_SWDIO: R17.1, U1.D4, U2.2
PROC_UART4_RX: U1.C4, U4.9
PROC_UART4_TX: U1.C10, U4.7
RST_OUT_U2_JTAG_RST_B: R15.1, U2.10, U16.1
VCC_S1_9V4: C39.1, C42.1, C43.1, J1.1, R30.2, U12.4
VCC_TIER1_3V3: C1.1, C2.1, C3.1, C4.1, C5.1, C6.1, C7.1, C8.1, C15.1, C16.1, C17.1, C25.1, C26.1, C27.1, C28.1, C30.1, C31.1, C32.1, C33.1, C37.1, C40.1, C41.1, C44.1, C45.1, F1.2, I1.2, R7.2, R8.2, R10.2, R12.2, R15.2, R16.2, R17.2, R20.2, R23.2, R24.2, R25.2, R31.1, R33.2, R34.2, R36.1, U1.A1, U1.A10, U1.B8, U1.E4, U1.E6, U1.F7, U2.1, U3.8, U4.6, U6.3, U6.5, U6.12, U6.18, U11.4, U12.5, U13.6, U16.5, U17.5

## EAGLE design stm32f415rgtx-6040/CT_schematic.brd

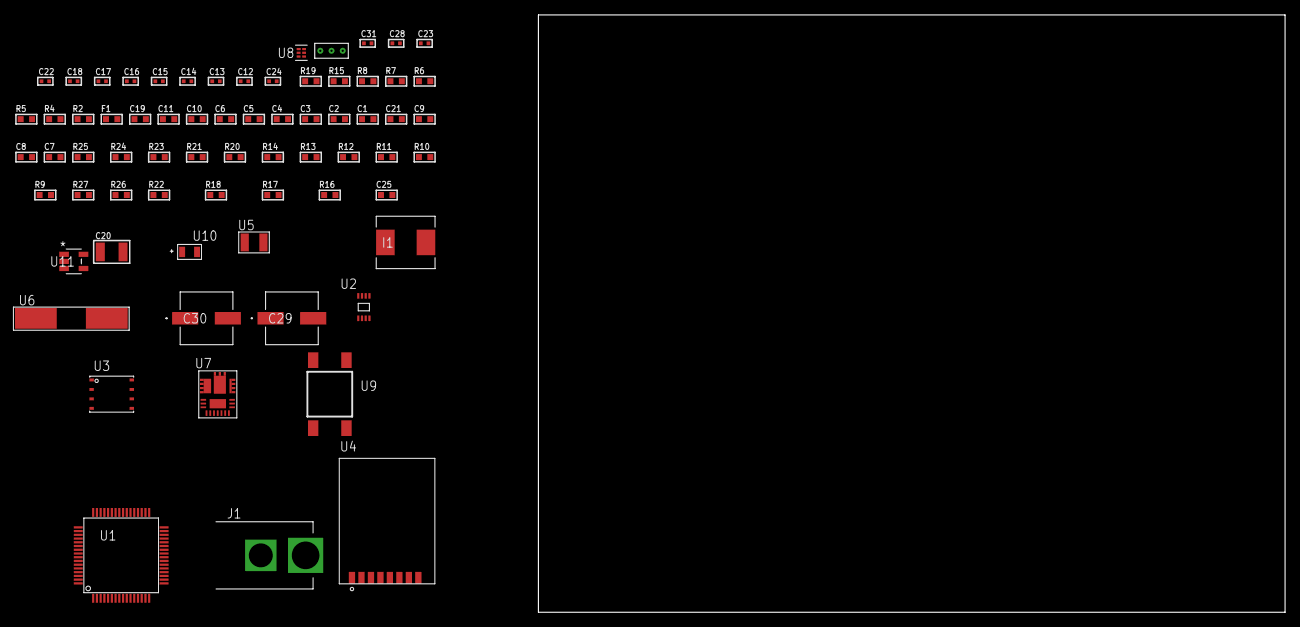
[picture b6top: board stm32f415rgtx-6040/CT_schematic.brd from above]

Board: 2 copper layers, 100.0 x 80.0 mm, 69 parts (0 on the bottom side), 41 nets, no tracks yet.

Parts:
C1, C11, C19: 1e-06; C0603
C2, C3, C4, C5, C6: 1e-07; C0603
C7: 4.7e-06; C0603
C8, C9, C21: 2.2e-06; C0603
C10: 1e-08; C0603
C12, C13, C14, C15: 1e-11; C0402
C16, C17, C31: 1e-08; C0402
C18, C22, C23, C28: 1e-07; C0402
C20: 0.0001; C1210
C24: 8.2e-09; C0402
C25: 2.7074646757046e-07; R0603
C29, C30: 0.0001; EXV-9H
F1: 240.0; L0603
I1: 6.8e-07; IND25X25CZ
J1: PJ-037B; PJ-037B_PACKAGE
R2: 1000.0; R0603
R4: 4700.0; R0603
R5, R6, R7, R8: 2200.0; R0603
R9, R10, R11, R12, R13, R14, R23, R24: 10000.0; R0603
R15: 0.1; R0603
R16: 4030.2416170974; R0603
R17: 1007.5604042744; R0603
R18: 64.186993865031; R0603
R19: 130.0; R0603
R20: 39000.0; R0603
R21: 49900.0; R0603
R22: 5322.6666666667; R0603
R25: 18000.0; R0603
R26: 470000.0; R0603
R27: 120000.0; R0603
U1: STM32F415RGT6; LQFP64
U2: 24AA00T-I/MNY; TDFN-8/6MM
U3: 24AA256-I/MF; DFN8-S
U4: RFM75-S
U5: ABS07-32.768KHZ-7-T
U6: ABLS-25.000MHZ-B2F-T
U7: IR3899MTR1PBF
U8: TPS3895ADRYR; SON-6
U9: 4-1437565-2; SW_4-1437565-2
U10: Q65110A2395; LGM67K-G1J2-24-Z
U11: nc7sz125m5x; NC7SZ125M5X
U12: Dummy; DUMMY_PACKAGE_138

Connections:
CLK_CRYSTAL_U1_3: C12.1, U1.3, U5.1
CLK_CRYSTAL_U1_4: C13.1, U1.4, U5.2
CLK_CRYSTAL_U1_5: C14.1, U1.5, U6.1
CLK_CRYSTAL_U1_6: C15.1, U1.6, U6.2
GND: C1.2, C2.2, C3.2, C4.2, C5.2, C6.2, C7.2, C8.2, C9.2, C10.2, C11.2, C12.2, C13.2, C14.2, C15.2, C16.2, C17.2, C18.2, C19.2, C21.2, C22.2, C23.2, C28.2, C29.2, C30.2, C31.2, J1.2, R2.2, R9.2, R11.2, R12.2, R15.1, R15.2, R17.2, R20.2, R22.2, R25.2, R27.2, U1.12, U1.18, U1.63, U2.4, U3.4, U4.1, U7.4, U7.11, U7.17, U8.2, U10.C, U11.1, U11.3, U12.1
NET_U1_7: R4.1, U1.7, U11.4
NET_U1_13: C10.1, C11.1, F1.1, U1.13
NET_U1_29: R7.1, U1.29, U2.6
NET_U1_30: R8.1, U1.30, U2.5
NET_U1_31: C8.1, U1.31
NET_U1_47: C9.1, U1.47
NET_U1_58: R5.1, U1.58, U3.6
NET_U1_59: R6.1, U1.59, U3.5
NET_U1_60: R9.1, U1.60
NET_U1_62: U9.3, U9.4
NET_U3_1: R10.1, U3.1
NET_U3_2: R11.1, U3.2
NET_U3_3: R12.1, U3.3
NET_U4_3: R13.1, U4.3
NET_U7_1: C24.1, R16.1, R17.1, R18.1, R19.1, U7.1, U7.8
NET_U7_2: C23.1, U7.2
NET_U7_3: C24.2, C25.1, C25.2, U7.3
NET_U7_5: R20.1, U7.5
NET_U7_10: C21.1, U7.10
NET_U7_12: C20.1, I1.1, U7.12
NET_U7_14: C20.2, U7.14
NET_U7_15: R21.1, R22.1, U7.15
NET_U7_ATNET_3: I1.2, R16.2
NET_U7_ATNET_4: C25.2, R18.2
NET_U8_1: R24.1, R25.1, U8.1
NET_U8_3: R26.2, R27.1, U8.3
NET_U8_4: R23.1, U8.4, U11.2
NET_U9_1: R2.1, U9.1, U9.2
PROC_SPI1_MISO: U1.22, U4.7
PROC_SPI1_MOSI: U1.23, U4.6
PROC_SPI1_NSS: R14.1, U1.20, U4.4
PROC_SPI1_SCK: U1.21, U4.5
PROC_TIM1_CH2: U1.42, U12.2
PROC_TIM1_CH4: U1.44, U12.3
VCC_S1_16V3: C22.1, C29.1, C30.1, J1.1, R21.2, U7.9
VCC_TIER1_2V5: C1.1, C2.1, C3.1, C4.1, C5.1, C6.1, C7.1, C16.1, C17.1, C18.1, C19.1, C28.1, C31.1, F1.2, I1.2, R4.2, R5.2, R6.2, R7.2, R8.2, R10.2, R13.2, R14.2, R16.2, R23.2, R24.2, R26.1, U1.1, U1.19, U1.32, U1.48, U1.64, U2.8, U3.7, U3.8, U4.2, U8.6, U11.5
